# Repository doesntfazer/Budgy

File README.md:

# Budgy Keyboard

Budgy is a split 34 key keyboard powered by a Raspberry Pi Pico and diode-less.

### Builds:

[Build by: Jakob Edvarsson](https://github.com/JakobEdvardsson)

## What you need to build a Budgy

| Component | Amount |
|--|--|
| Reversible Budgy PCB | x2 |
| Raspberry Pi Pico w/headers | x2 |
| Cherry Switches (5 pin recommended) | x34 |
| Keycaps | x34 |
| TRRS Cable | x1 |
| PJ-320A TRRS Jacks | x2 |
| Rubber Bumpers | x8 |

- Solder headers to both raspberry pi Pico's

- On the left hand board, solder the Raspberry Pi Pico facing up and to the rightmost set of pins. If you are still unsure reference the photo above.

- Like in the previous step above, on the right hand side of the board, solder the Pico to the rightmost set of pins. Use the photo for reference. 

- Solder the TRRS Jacks to the top of each side, again reference photo. 

- I recommended at this point, you test the board to make sure everything is functioning. Plug in each side of the board while holding down the reset pin on the top of the board. Drag and drop the UF2 files from [here.](https://github.com/doesntfazer/Keyboard-Dweebs-Firmware-repository/tree/main/VIAL-QMK/budgy) You need to do this on both boards.

- Connect the halves using a TRRS cable, and short each key using some tweezers or a piece of wire. These files use [Vial QMK. You can download this app and use it to configure your keyboard.](https://get.vial.today/download/)

- If everything is working correctly you can proceed to solder in all of the switches, add your keycaps, and put a rubber bumper in each corner on the bottom of each pcb, then start typing away.

### Firmware

Here are links to a couple of different firmware available for the Budgy keyboard. 

- VIAL [here.](https://github.com/doesntfazer/Keyboard-Dweebs-Firmware-repository/tree/main/VIAL-QMK/budgy)
- KMK - [here.](https://github.com/KMKfw/kmk_firmware/tree/master/boards/budgy)
- QMK - [here.](https://github.com/qmk/qmk_firmware/tree/master/keyboards/budgy)

#### Some things to note. 
- It's okay if you don't have 5 pin Cherry switches. If you bend one of the pins on the switch a bit, they should hold in place when you flip the board over.

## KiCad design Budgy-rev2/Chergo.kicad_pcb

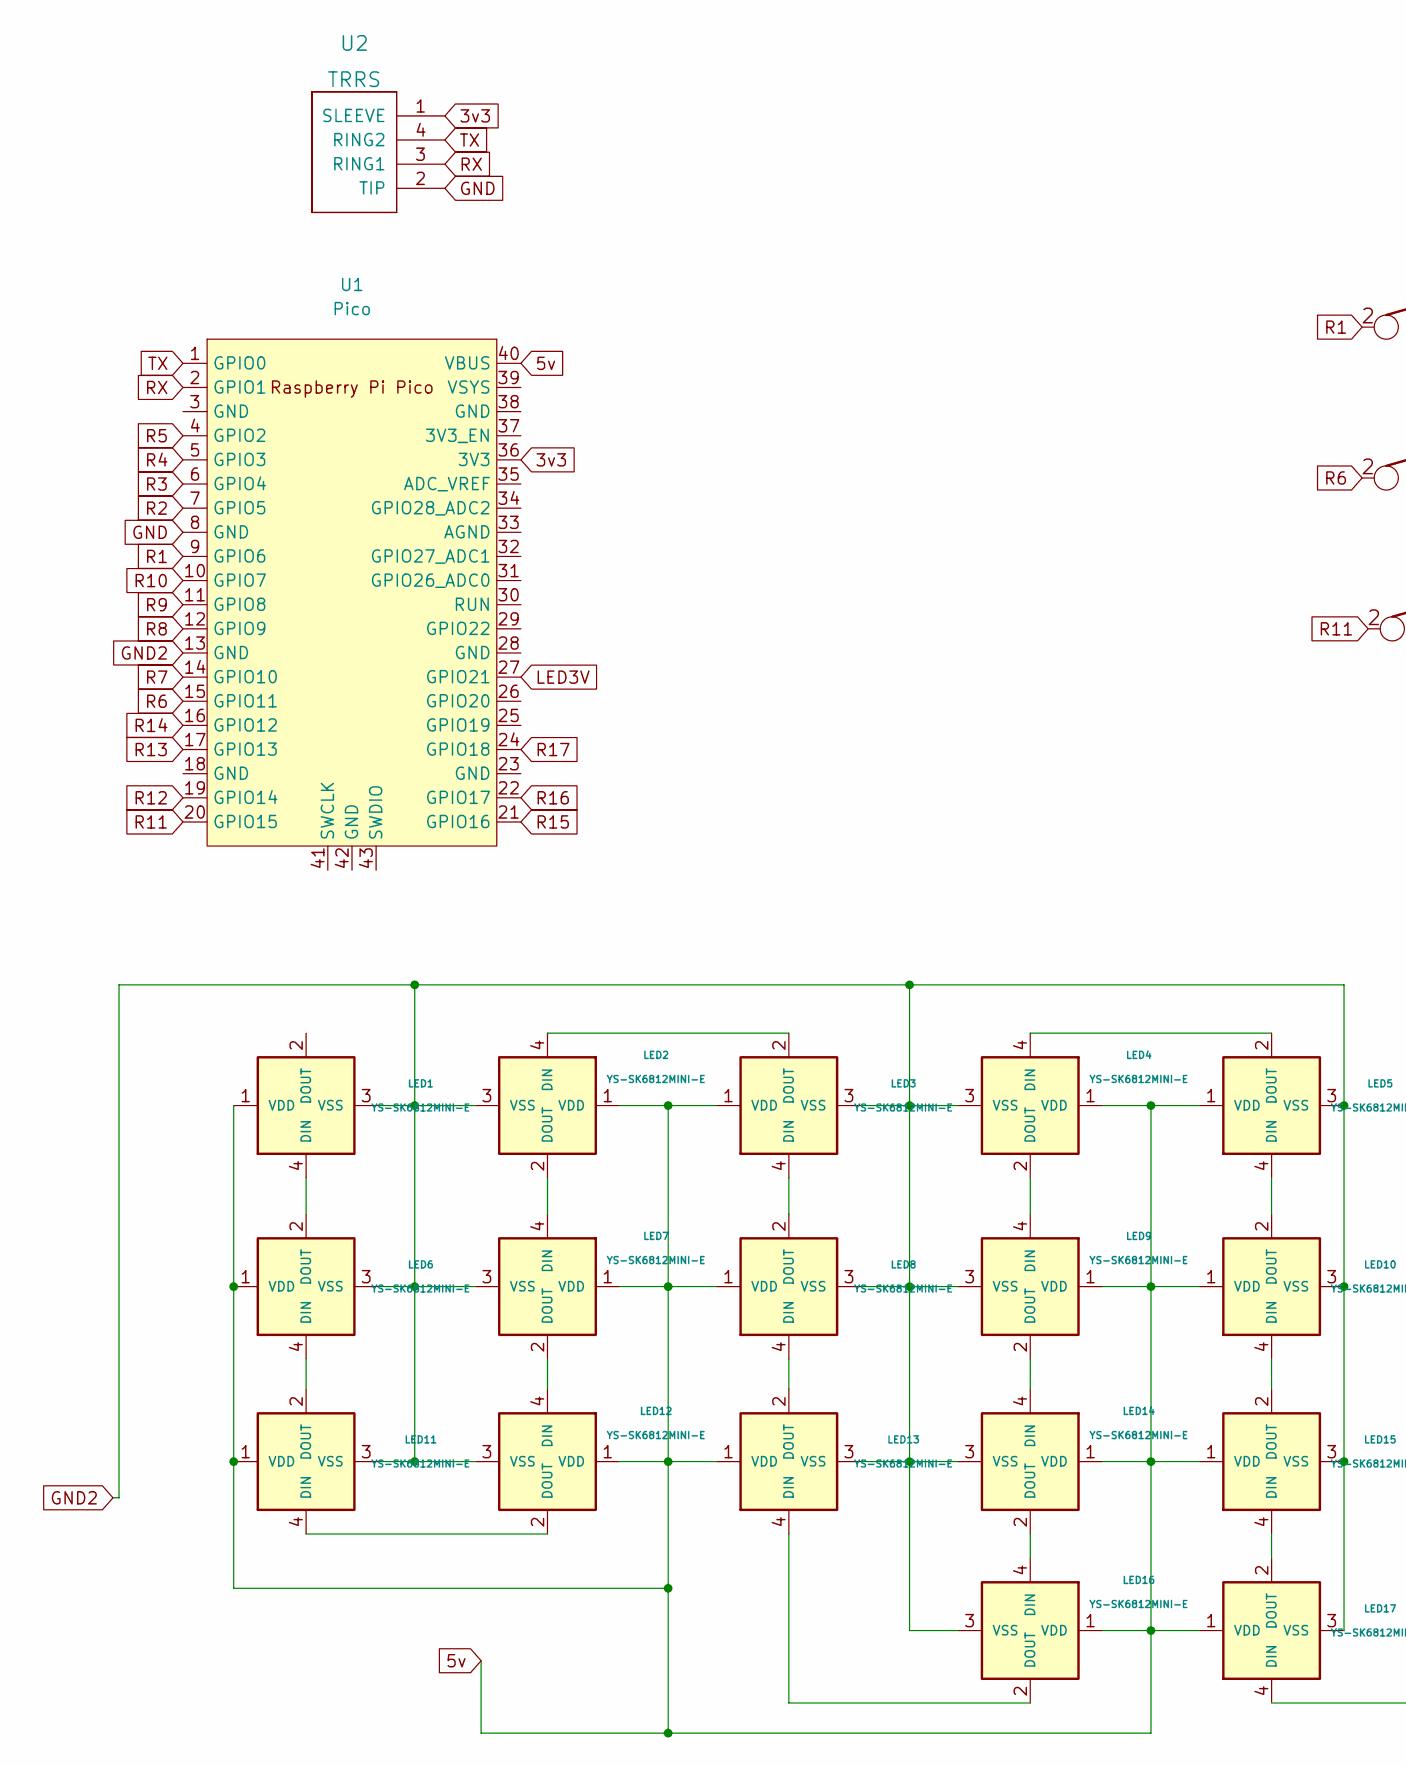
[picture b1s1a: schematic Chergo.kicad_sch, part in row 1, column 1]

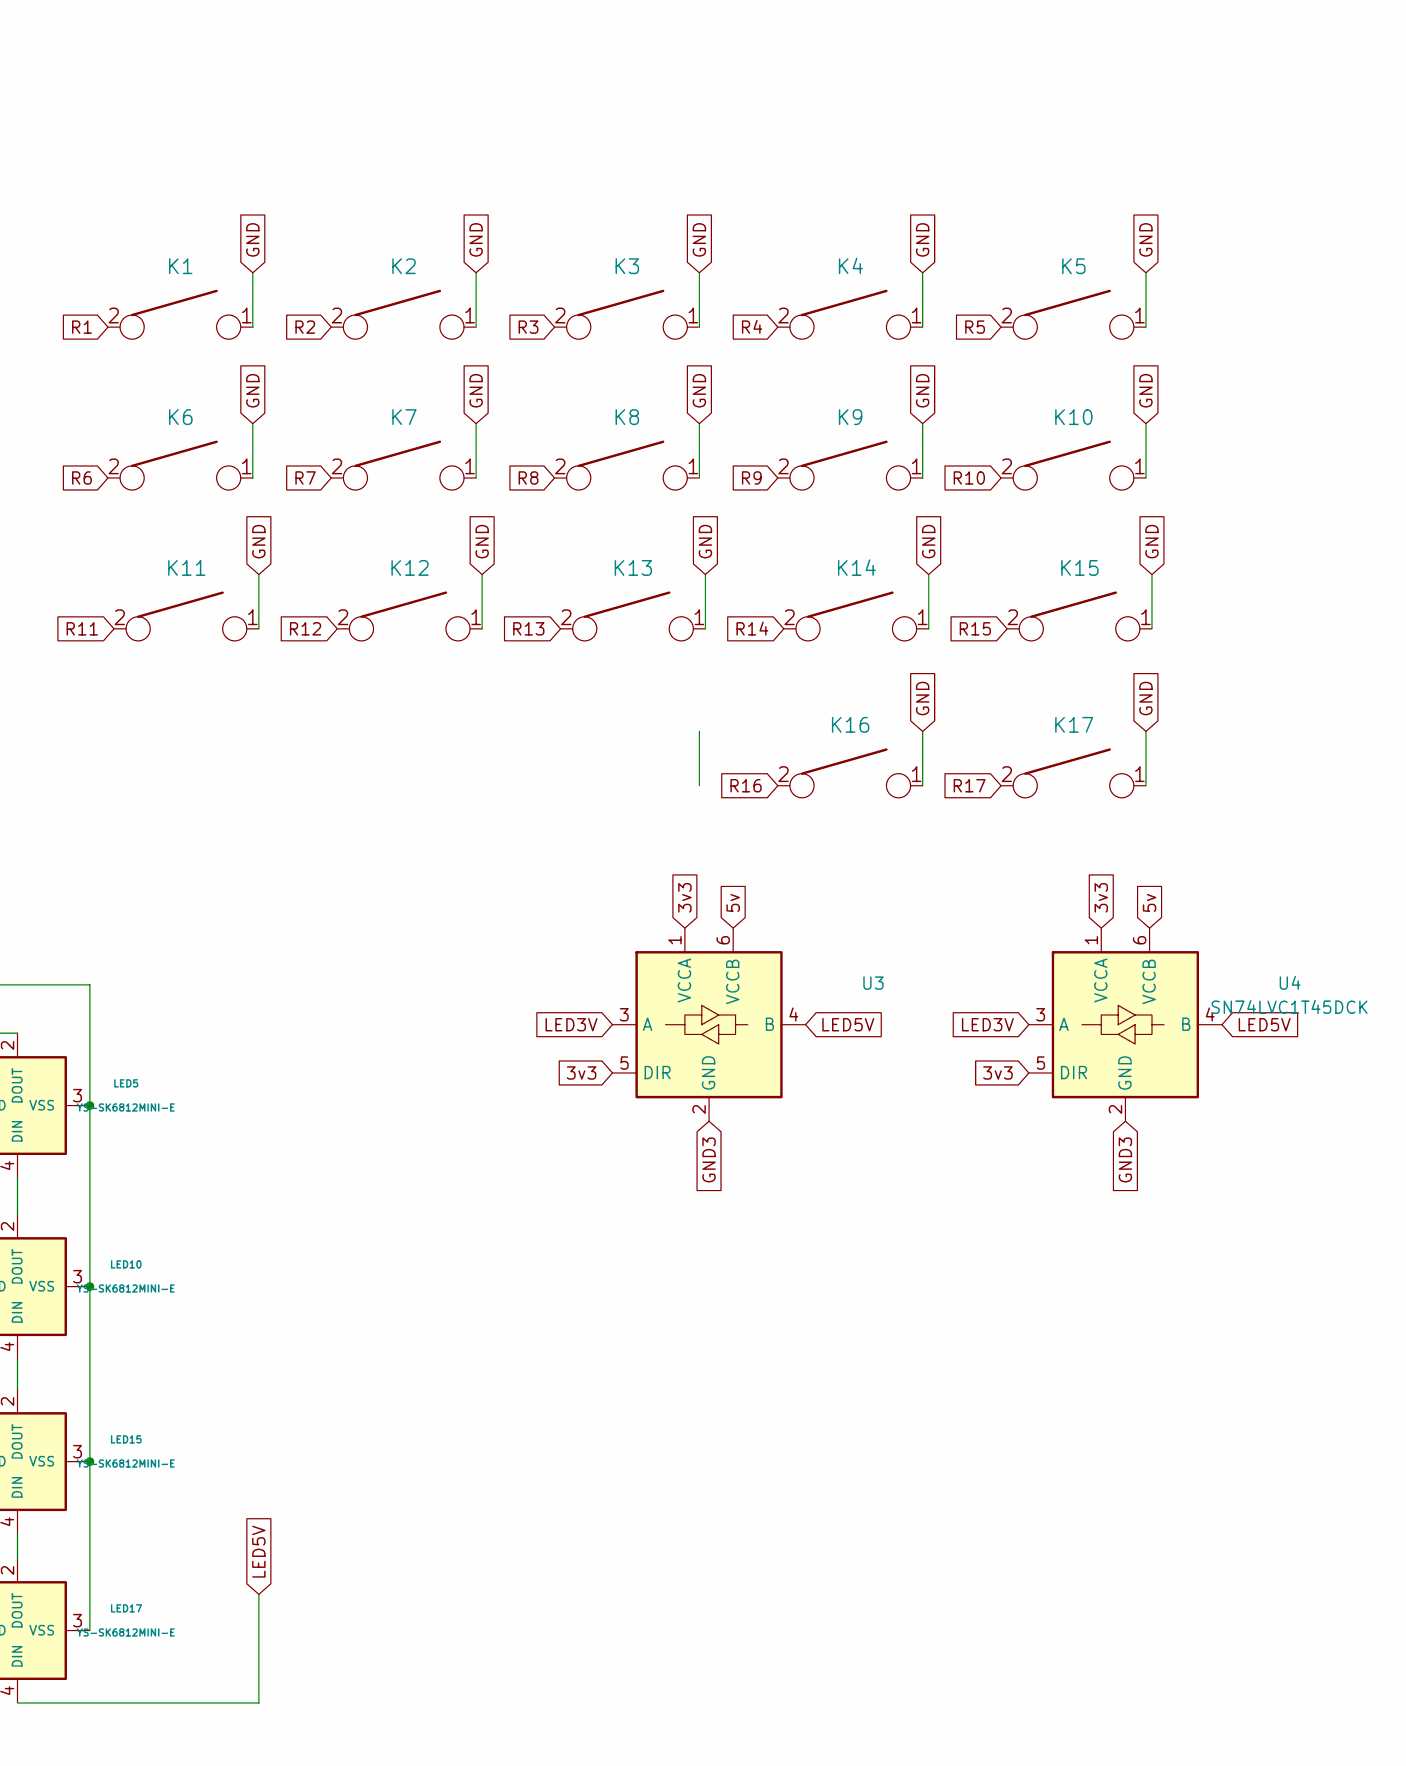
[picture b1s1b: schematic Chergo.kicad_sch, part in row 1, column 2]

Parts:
K1, K2, K3, K4, K5, K6, K7, K8, K9, K10, K11, K12, K13, K14, K15, K16, K17: KEYSW; SW_MX_reversible
LED1, LED2, LED3, LED4, LED5, LED6, LED7, LED8, LED9, LED10, LED11, LED12, LED13, LED14, LED15, LED16, LED17: YS-SK6812MINI-E; YS-SK6812MINI-E-reversible-fix
U1: Pico; RPi_Pico_SMD_TH-REV2
U2: TRRS; TRRS-PJ-320A-rev
U3: (no value)
U4: SN74LVC1T45DCK; SOT-363_SC-70-6

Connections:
3v3: U1.36 (3V3), U2.1 (SLEEVE), U3.1 (VCCA), U3.5 (DIR), U4.1 (VCCA), U4.5 (DIR)
5v: LED1.1 (VDD), LED2.1 (VDD), LED3.1 (VDD), LED4.1 (VDD), LED5.1 (VDD), LED6.1 (VDD), LED7.1 (VDD), LED8.1 (VDD), LED9.1 (VDD), LED10.1 (VDD), LED11.1 (VDD), LED12.1 (VDD), LED13.1 (VDD), LED14.1 (VDD), LED15.1 (VDD), LED16.1 (VDD), LED17.1 (VDD), U1.40 (VBUS), U3.6 (VCCB), U4.6 (VCCB)
GND: K1.1, K2.1, K3.1, K4.1, K5.1, K6.1, K7.1, K8.1, K9.1, K10.1, K11.1, K12.1, K13.1, K14.1, K15.1, K16.1, K17.1, U1.8 (GND), U2.2 (TIP)
GND2: LED1.3 (VSS), LED2.3 (VSS), LED3.3 (VSS), LED4.3 (VSS), LED5.3 (VSS), LED6.3 (VSS), LED7.3 (VSS), LED8.3 (VSS), LED9.3 (VSS), LED10.3 (VSS), LED11.3 (VSS), LED12.3 (VSS), LED13.3 (VSS), LED14.3 (VSS), LED15.3 (VSS), LED16.3 (VSS), LED17.3 (VSS), U1.13 (GND)
GND3: U3.2 (GND), U4.2 (GND)
LED3V: U1.27 (GPIO21), U3.3 (A), U4.3 (A)
LED5V: LED17.4 (DIN), U3.4 (B), U4.4 (B)
unnamed: LED1.4 (DIN), LED6.2 (DOUT)
unnamed: LED2.2 (DOUT), LED7.4 (DIN)
unnamed: LED2.4 (DIN), LED3.2 (DOUT)
unnamed: LED3.4 (DIN), LED8.2 (DOUT)
unnamed: LED4.2 (DOUT), LED9.4 (DIN)
unnamed: LED4.4 (DIN), LED5.2 (DOUT)
unnamed: LED5.4 (DIN), LED10.2 (DOUT)
unnamed: LED10.4 (DIN), LED15.2 (DOUT)
unnamed: LED6.4 (DIN), LED11.2 (DOUT)
unnamed: LED11.4 (DIN), LED12.2 (DOUT)
unnamed: LED7.2 (DOUT), LED12.4 (DIN)
unnamed: LED8.4 (DIN), LED13.2 (DOUT)
unnamed: LED13.4 (DIN), LED16.2 (DOUT)
unnamed: LED14.2 (DOUT), LED16.4 (DIN)
unnamed: LED9.2 (DOUT), LED14.4 (DIN)
unnamed: LED15.4 (DIN), LED17.2 (DOUT)
R1: K1.2, U1.9 (GPIO6)
R2: K2.2, U1.7 (GPIO5)
R3: K3.2, U1.6 (GPIO4)
R4: K4.2, U1.5 (GPIO3)
R5: K5.2, U1.4 (GPIO2)
R6: K6.2, U1.15 (GPIO11)
R7: K7.2, U1.14 (GPIO10)
R8: K8.2, U1.12 (GPIO9)
R9: K9.2, U1.11 (GPIO8)
R10: K10.2, U1.10 (GPIO7)
R11: K11.2, U1.20 (GPIO15)
R12: K12.2, U1.19 (GPIO14)
R13: K13.2, U1.17 (GPIO13)
R14: K14.2, U1.16 (GPIO12)
R15: K15.2, U1.21 (GPIO16)
R16: K16.2, U1.22 (GPIO17)
R17: K17.2, U1.24 (GPIO18)
RX: U1.2 (GPIO1), U2.3 (RING1)
TX: U1.1 (GPIO0), U2.4 (RING2)

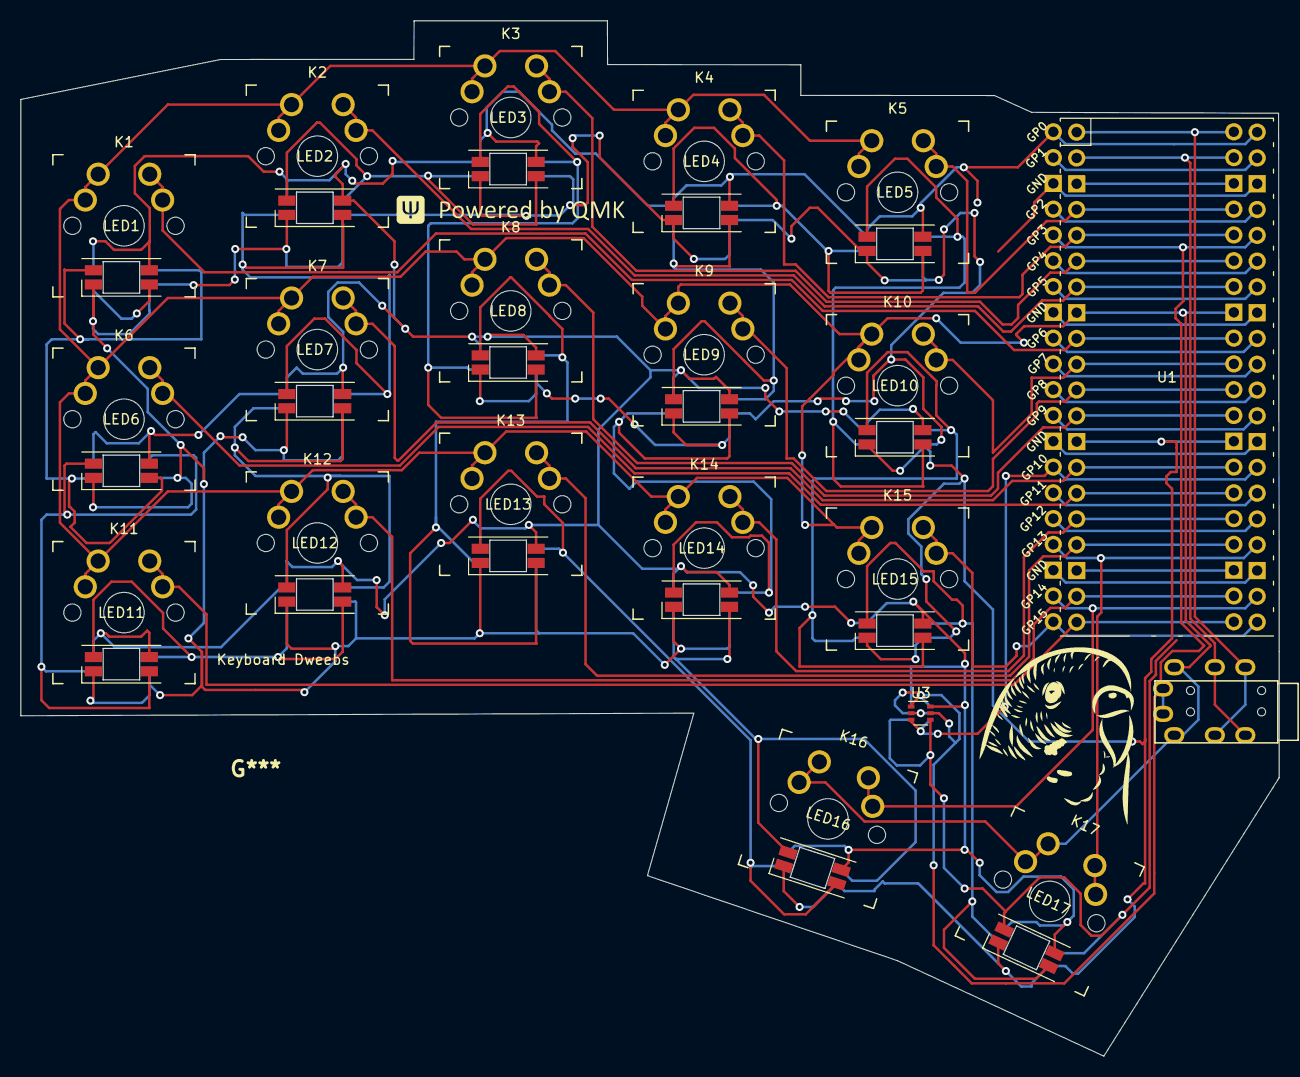
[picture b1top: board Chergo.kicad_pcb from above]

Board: 2 copper layers, 123.9 x 102.0 mm, 38 parts (1 on the bottom side), 42 nets.

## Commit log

2022-11-15 added silkscreen
2022-11-15 silkscreen footprints
2022-11-16 moved to rev1 folder
2022-11-19 rev2
2022-11-19 changed to 5v for rgbled
2022-11-19 added fill zones
2022-11-19 removed clutter
2022-11-25 add voltage divider
2022-12-23 updates to rev2
2022-12-23 adding build guide
2024-04-05 Added build image. Moved README file
